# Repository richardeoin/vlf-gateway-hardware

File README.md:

EAGLE CAD Design files for the VLF Gateway Unit

## Photo

## Design Notes

The board is based around a NXP
[LPC1766](http://www.nxp.com/documents/data_sheet/LPC1769_68_67_66_65_64_63.pdf)
ARM Cortex-M3 microcontroller. A good proportion of the board area is
given over to the ethernet PHY (an
[SMSC8720](http://www.smsc.com/media/Downloads_Public/Data_Sheets/8720a.pdf))
and connector. A small EEPROM that comes pre-programmed with a
globally unique ethernet MAC address is also included.

Data is received from the remote unit using an
[AT86RF212](http://www.atmel.com/images/doc8168.pdf) 868MHz radio and
stored on a micro SD card.

## [License](LICENSE.md)

[MIT](http://opensource.org/licenses/MIT)

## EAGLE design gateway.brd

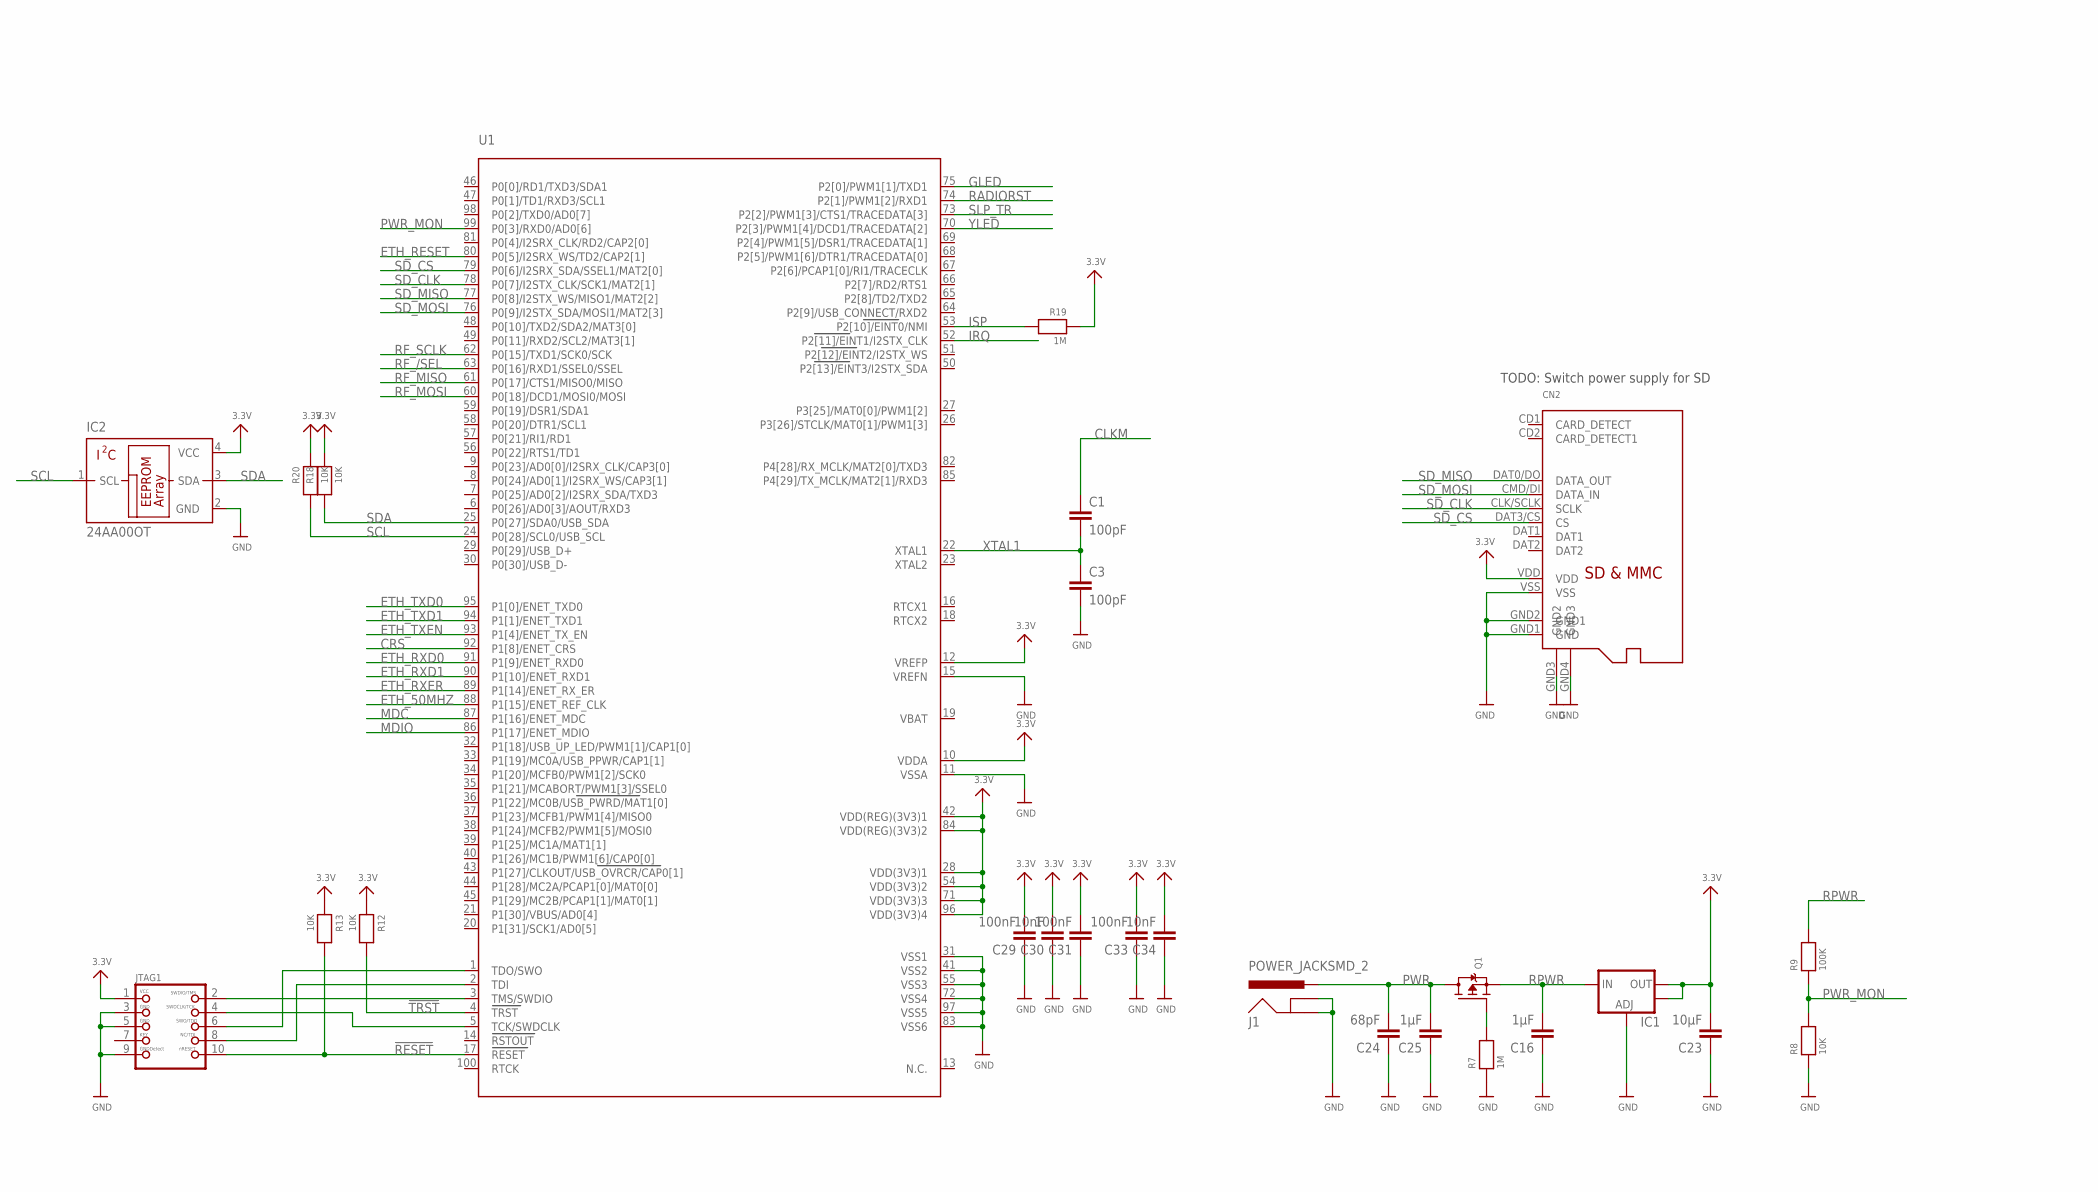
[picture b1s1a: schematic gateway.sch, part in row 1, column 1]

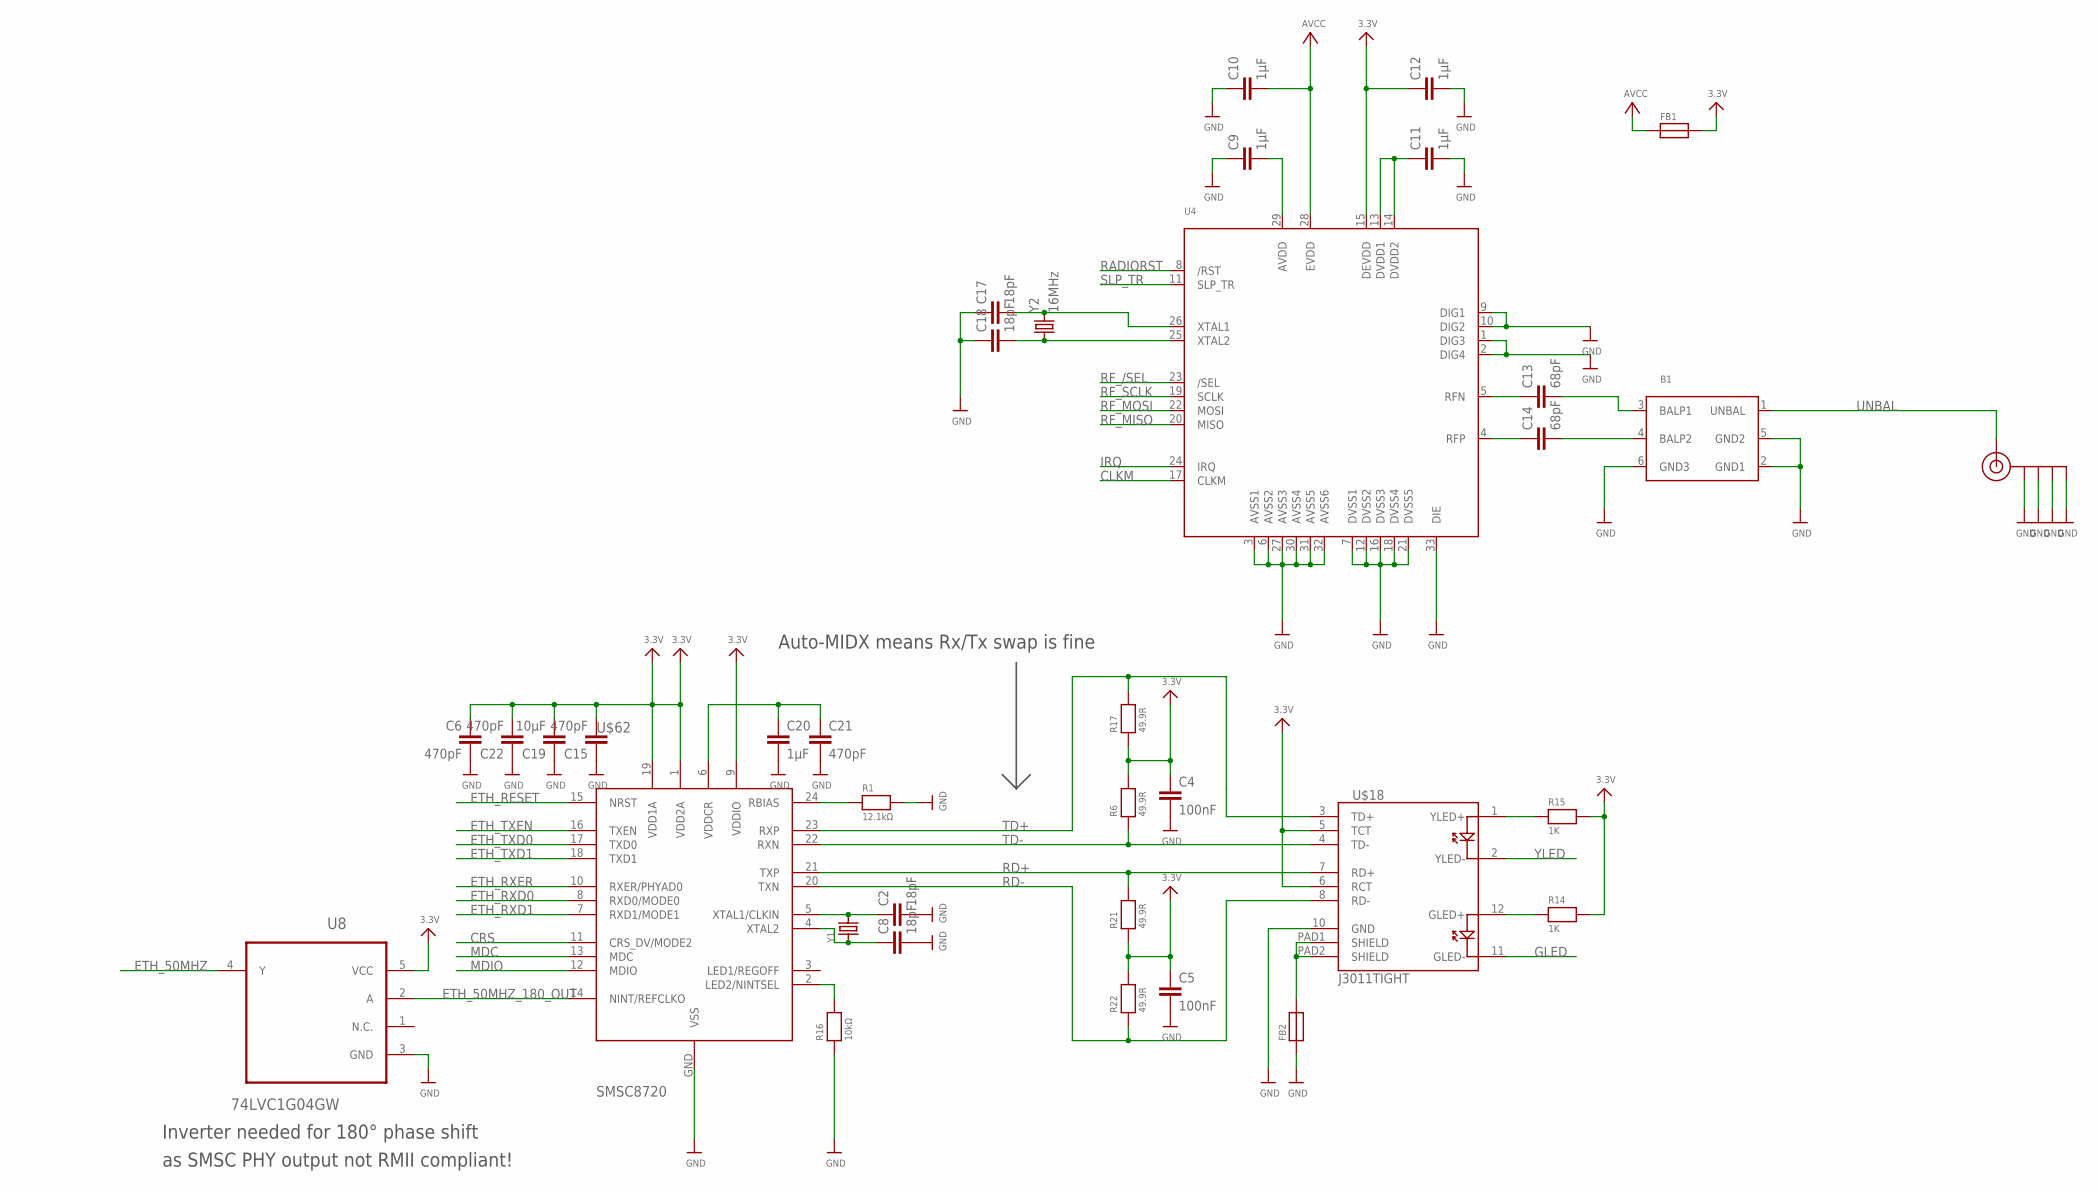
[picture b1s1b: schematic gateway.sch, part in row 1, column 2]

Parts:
B1: BALUN+LP; BALUN0805
C1, C3: 100pF; C0603K
C2, C8, C17, C18: 18pF; C0603K
C4, C5: 100nF; C1206
C6, C15, C21, C22: 470pF; C0603K
C9, C10, C11, C12, C16, C20, C25: 1µF; C0603K
C13, C14, C24: 68pF; C0603K
C19, C23: 10µF; C0603K
C29, C31, C33: 100nF; C0603K
C30, C34: 10nF; C0603K
CN2: MICROSDDM3B; MICROSD_DM3B
FB1, FB2: FERRITE; 0603
IC1: V_REG_LM1117SOT223; SOT223
IC2: 24AA00OT; SOT23-5L
J1: POWER_JACKSMD_2; POWER_JACK_SMD_2
J$1: SMA_EDGE; SMA-EDGE
JTAG1: JTAG-CORTEXM3; 2X05_1.27MM_SMT
Q1: MOSFET-P; SOT23-R
R1: 12.1kΩ; 0603-MINI
R6, R17, R21, R22: 49.9R; 0603-MINI
R7, R19: 1M; 0603-MINI
R8, R12, R13, R18, R20: 10K; 0603-MINI
R9: 100K; 0603-MINI
R14, R15: 1K; 0603-MINI
R16: 10kΩ; 0603-MINI
U1: LPC1768; LQFP100
U4: AT86RF212; 32QN2
U8: 74LVC1G04GW; SOT65P210X110-5N
U$18: J3011TIGHT; J3011_TIGHT
U$62: SMSC8720; QFN24_SMSC8720
Y1: CRYSTALTHIN32K; CRYSTAL_4.9X1.8
Y2: 16MHz; CRYSTAL-SMD-5X3

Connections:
3.3V: C4.1, C5.1, C6.1, C12.1, C15.2, C19.2, C22.2, C23.2, C29.2, C30.2, C31.2, C33.2, C34.2, CN2.VDD, FB1.2, IC1.2 (OUT), IC1.4 (OUT), IC2.4 (VCC), JTAG1.1, R6.2, R12.1, R13.1, R14.2, R15.2, R17.1, R18.1, R19.1, R20.1, R21.1, R22.2, U1.10 (VDDA), U1.12 (VREFP), U1.28 (VDD(3V3)1), U1.42 (VDD(REG)(3V3)1), U1.54 (VDD(3V3)2), U1.71 (VDD(3V3)3), U1.84 (VDD(REG)(3V3)2), U1.96 (VDD(3V3)4), U4.15 (DEVDD), U8.5 (VCC), U$18.5 (TCT), U$18.6 (RCT), U$62.1 (VDD2A), U$62.9 (VDDIO), U$62.19 (VDD1A)
!RESET!: JTAG1.10, R13.2, U1.17 (RESET)
!TRST!: R12.2, U1.4 (TRST)
AVCC: C10.2, FB1.1, U4.28 (EVDD)
AVDD-IN: C9.2, U4.29 (AVDD)
BALP1: B1.3 (BALP1), C13.2
BALP2: B1.4 (BALP2), C14.2
CGND: FB2.2, U$18.PAD1 (SHIELD), U$18.PAD2 (SHIELD)
CLKM: C1.1, U4.17 (CLKM)
CRS: U1.92 (P1[8]/ENET_CRS), U$62.11 (CRS_DV/MODE2)
ETH_50MHZ: U1.88 (P1[15]/ENET_REF_CLK), U8.4 (Y)
ETH_50MHZ_180_OUT: U8.2 (A), U$62.14 (NINT/REFCLKO)
ETH_RESET: U1.80 (P0[5]/I2SRX_WS/TD2/CAP2[1]), U$62.15 (NRST)
ETH_RXD0: U1.91 (P1[9]/ENET_RXD0), U$62.8 (RXD0/MODE0)
ETH_RXD1: U1.90 (P1[10]/ENET_RXD1), U$62.7 (RXD1/MODE1)
ETH_RXER: U1.89 (P1[14]/ENET_RX_ER), U$62.10 (RXER/PHYAD0)
ETH_TXD0: U1.95 (P1[0]/ENET_TXD0), U$62.17 (TXD0)
ETH_TXD1: U1.94 (P1[1]/ENET_TXD1), U$62.18 (TXD1)
ETH_TXEN: U1.93 (P1[4]/ENET_TX_EN), U$62.16 (TXEN)
GLED: U1.75 (P2[0]/PWM1[1]/TXD1), U$18.11 (GLED-)
GLED+: R14.1, U$18.12 (GLED+)
GND: B1.2 (GND1), B1.5 (GND2), B1.6 (GND3), C2.2, C3.2, C4.2, C5.2, C6.2, C8.2, C9.1, C10.1, C11.2, C12.2, C15.1, C16.1, C17.1, C18.1, C19.1, C20.2, C21.2, C22.1, C23.1, C24.1, C25.1, C29.1, C30.1, C31.1, C33.1, C34.1, CN2.GND1 (GND), CN2.GND2 (GND1), CN2.GND3 (GND2), CN2.GND4 (GND3), CN2.VSS, FB2.1, IC1.1 (ADJ), IC2.2 (GND), J1.GND (GNDBREAK), J1.P$4 (GND), J$1.GND@0 (GND), J$1.GND@1 (GND), J$1.GND@2 (GND), J$1.GND@3 (GND), JTAG1.3, JTAG1.5, JTAG1.9, R1.2, R7.1, R8.1, R16.1, U1.11 (VSSA), U1.15 (VREFN), U1.31 (VSS1), U1.41 (VSS2), U1.55 (VSS3), U1.72 (VSS4), U1.83 (VSS6), U1.97 (VSS5), U4.1 (DIG3), U4.2 (DIG4), U4.3 (AVSS1), U4.6 (AVSS2), U4.7 (DVSS1), U4.9 (DIG1), U4.10 (DIG2), U4.12 (DVSS2), U4.16 (DVSS3), U4.18 (DVSS4), U4.21 (DVSS5), U4.27 (AVSS3), U4.30 (AVSS4), U4.31 (AVSS5), U4.32 (AVSS6), U4.33 (DIE), U8.3 (GND), U$18.10 (GND), U$62.GND (VSS)
IRQ: U1.52 (P2[11]/EINT1/I2STX_CLK), U4.24 (IRQ)
ISP: R19.2, U1.53 (P2[10]/EINT0/NMI)
MDC: U1.87 (P1[16]/ENET_MDC), U$62.13 (MDC)
MDIO: U1.86 (P1[17]/ENET_MDIO), U$62.12 (MDIO)
unnamed: C11.1, U4.13 (DVDD1), U4.14 (DVDD2)
unnamed: R16.2, U$62.2 (LED2/NINTSEL)
unnamed: C2.1, U$62.5 (XTAL1/CLKIN), Y1.2
unnamed: C8.1, U$62.4 (XTAL2), Y1.1
PWR: C24.2, C25.2, J1.VIN0 (PWR), Q1.3 (D)
PWR_MON: R8.2, R9.1, U1.99 (P0[3]/RXD0/AD0[6])
Q1DOWN: Q1.1 (G), R7.2
RADIORST: U1.74 (P2[1]/PWM1[2]/RXD1), U4.8 (/RST)
RBIAS: R1.1, U$62.24 (RBIAS)
RD+: R21.2, U$18.7 (RD+), U$62.21 (TXP)
RD-: R22.1, U$18.8 (RD-), U$62.20 (TXN)
RFN: C13.1, U4.5 (RFN)
RFP: C14.1, U4.4 (RFP)
RF_/SEL: U1.63 (P0[16]/RXD1/SSEL0/SSEL), U4.23 (/SEL)
RF_MISO: U1.61 (P0[17]/CTS1/MISO0/MISO), U4.20 (MISO)
RF_MOSI: U1.60 (P0[18]/DCD1/MOSI0/MOSI), U4.22 (MOSI)
RF_SCLK: U1.62 (P0[15]/TXD1/SCK0/SCK), U4.19 (SCLK)
RF_XTAL1: C17.2, U4.26 (XTAL1), Y2.3 (2)
RF_XTAL2: C18.2, U4.25 (XTAL2), Y2.1
RPWR: C16.2, IC1.3 (IN), Q1.2 (S), R9.2
SCL: IC2.1 (SCL), R20.2, U1.24 (P0[28]/SCL0/USB_SCL)
SDA: IC2.3 (SDA), R18.2, U1.25 (P0[27]/SDA0/USB_SDA)
SD_CLK: CN2.CLK/SCLK (SCLK), U1.78 (P0[7]/I2STX_CLK/SCK1/MAT2[1])
SD_CS: CN2.DAT3/CS (CS), U1.79 (P0[6]/I2SRX_SDA/SSEL1/MAT2[0])
SD_MISO: CN2.DAT0/DO (DATA_OUT), U1.77 (P0[8]/I2STX_WS/MISO1/MAT2[2])
SD_MOSI: CN2.CMD/DI (DATA_IN), U1.76 (P0[9]/I2STX_SDA/MOSI1/MAT2[3])
SLP_TR: U1.73 (P2[2]/PWM1[3]/CTS1/TRACEDATA[3]), U4.11 (SLP_TR)
TCK_SWDCLK: JTAG1.4, U1.5 (TCK/SWDCLK)
TD+: R17.2, U$18.3 (TD+), U$62.23 (RXP)
TD-: R6.1, U$18.4 (TD-), U$62.22 (RXN)
TDI: JTAG1.8, U1.2 (TDI)
TDO_SWO: JTAG1.6, U1.1 (TDO/SWO)
TMS_SWDIO: JTAG1.2, U1.3 (TMS/SWDIO)
UNBAL: B1.1 (UNBAL), J$1.SIG (SIGNAL)
VBAT: U1.19 (VBAT)
VDDCR: C20.1, C21.1, U$62.6 (VDDCR)
XTAL1: C1.2, C3.1, U1.22 (XTAL1)
YLED: U1.70 (P2[3]/PWM1[4]/DCD1/TRACEDATA[2]), U$18.2 (YLED-)
YLED+: R15.1, U$18.1 (YLED+)

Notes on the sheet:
TODO: Switch power supply for SD
Inverter needed for 180° phase shift
as SMSC PHY output not RMII compliant!
Auto-MIDX means Rx/Tx swap is fine

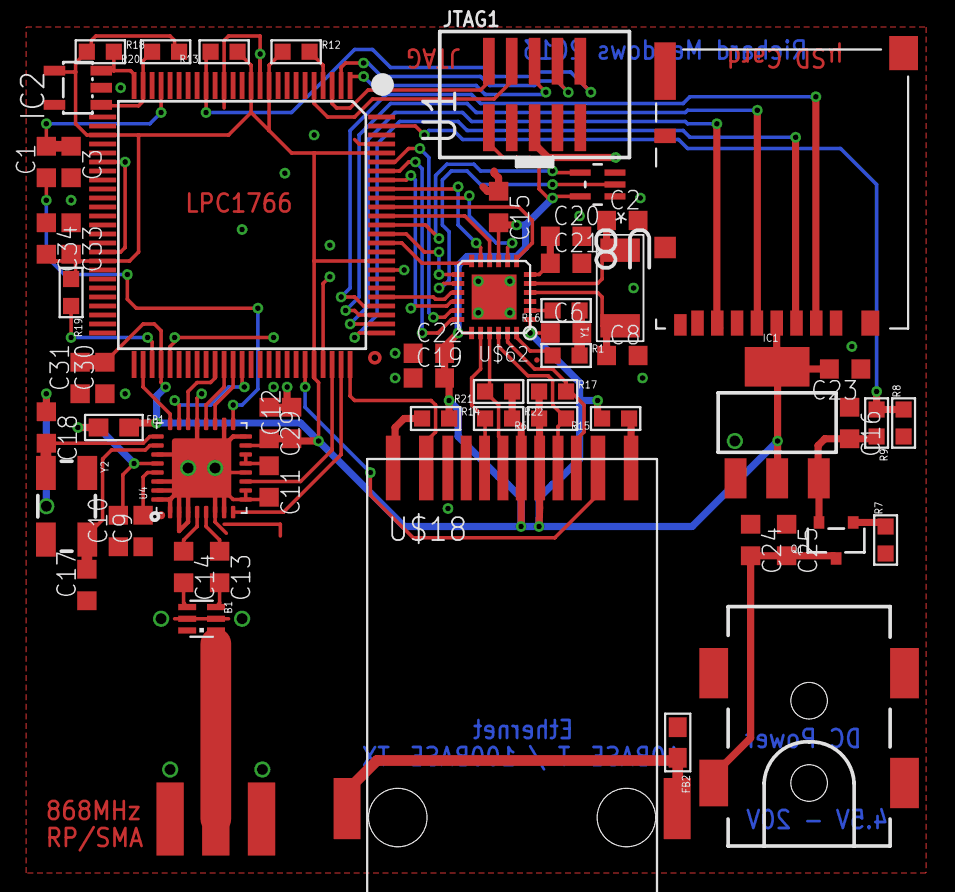
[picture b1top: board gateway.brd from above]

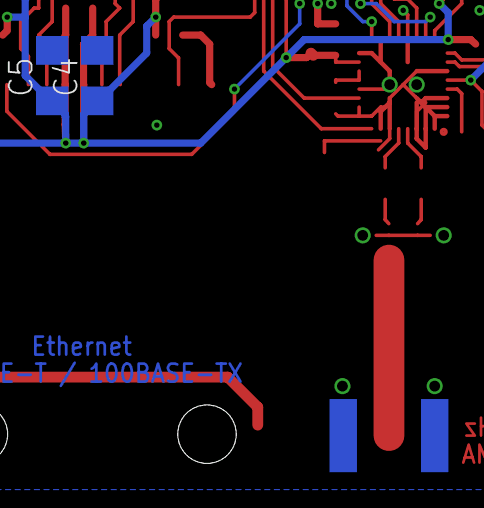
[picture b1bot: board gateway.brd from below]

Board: 2 copper layers, 62 parts (2 on the bottom side), 64 nets.

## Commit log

2013-10-28 Hardware Version 1
2013-10-28 Version 2
2013-10-28 Version 3
2013-10-28 Version 4
2013-10-28 Version 5
2013-10-28 Version 6
2013-10-28 Added photo
2013-10-28 Added basic README and LICENSE
2013-10-28 Wrote design notes
2013-10-28 Made photo link work
2013-10-29 Spelling fix

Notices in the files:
parts and their libraries:
SparkFun-Connectors: Licensing: CC v3.0 Share-Alike You are welcome to use this library for commercial purposes.
microbuilder_v3: This work is placed in the public domain, and may be freely used for commercial and non-commercial work with the following conditions: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
